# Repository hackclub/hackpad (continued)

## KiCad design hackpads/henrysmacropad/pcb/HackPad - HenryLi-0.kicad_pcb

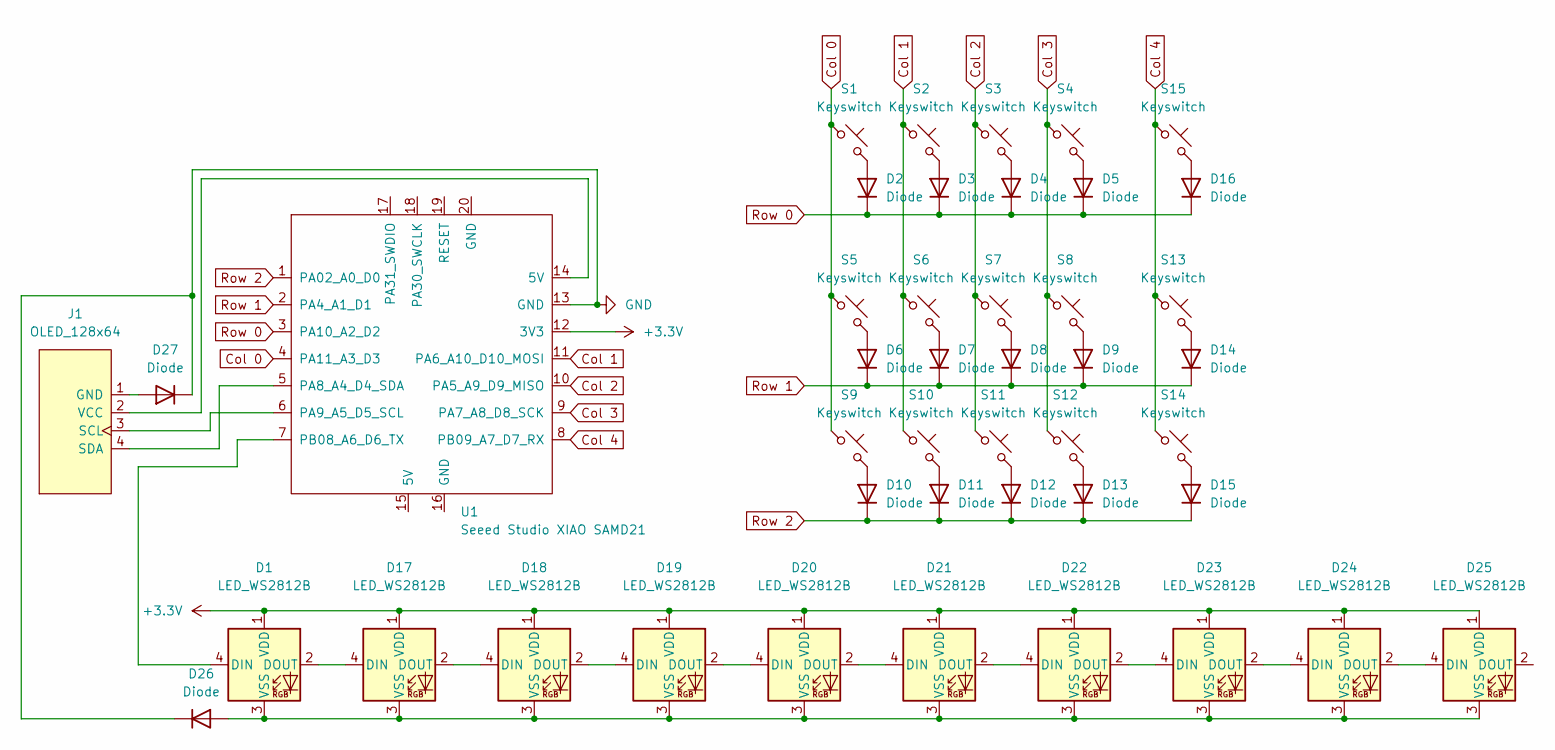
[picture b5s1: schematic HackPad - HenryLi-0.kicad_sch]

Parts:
D1, D17, D18, D19, D20, D21, D22, D23, D24, D25: LED_WS2812B
D2, D3, D4, D5, D6, D7, D8, D9, D10, D11, D12, D13, D14, D15, D16, D26, D27: Diode; Diode_DO-35
J1: OLED_128x64; SSD1306 128x64 OLED
S1, S2, S3, S4, S5, S6, S7, S8, S9, S10, S11, S12, S13, S14, S15: Keyswitch; SW_Cherry_MX_1.00u_PCB
U1: Seeed Studio XIAO SAMD21; XIAO-Generic-Thruhole-14P-2.54-21X17.8MM

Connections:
+3.3V: D1.1 (VDD), D17.1 (VDD), D18.1 (VDD), D19.1 (VDD), D20.1 (VDD), D21.1 (VDD), D22.1 (VDD), D23.1 (VDD), D24.1 (VDD), D25.1 (VDD), U1.12 (3V3)
Col 0: S1.1, S5.1, S9.1, U1.4 (PA11_A3_D3)
Col 1: S2.1, S6.1, S10.1, U1.11 (PA6_A10_D10_MOSI)
Col 2: S3.1, S7.1, S11.1, U1.10 (PA5_A9_D9_MISO)
Col 3: S4.1, S8.1, S12.1, U1.9 (PA7_A8_D8_SCK)
Col 4: S13.1, S14.1, S15.1, U1.8 (PB09_A7_D7_RX)
GND: D26.1 (K), D27.1 (K), U1.13 (GND)
unnamed: D1.4 (DIN), U1.7 (PB08_A6_D6_TX)
unnamed: D1.2 (DOUT), D17.4 (DIN)
unnamed: D1.3 (VSS), D17.3 (VSS), D18.3 (VSS), D19.3 (VSS), D20.3 (VSS), D21.3 (VSS), D22.3 (VSS), D23.3 (VSS), D24.3 (VSS), D25.3 (VSS), D26.2 (A)
unnamed: D2.2 (A), S1.2
unnamed: D3.2 (A), S2.2
unnamed: D4.2 (A), S3.2
unnamed: D5.2 (A), S4.2
unnamed: D6.2 (A), S5.2
unnamed: D7.2 (A), S6.2
unnamed: D8.2 (A), S7.2
unnamed: D9.2 (A), S8.2
unnamed: D10.2 (A), S9.2
unnamed: D11.2 (A), S10.2
unnamed: D12.2 (A), S11.2
unnamed: D13.2 (A), S12.2
unnamed: D14.2 (A), S13.2
unnamed: D15.2 (A), S14.2
unnamed: D16.2 (A), S15.2
unnamed: D17.2 (DOUT), D18.4 (DIN)
unnamed: D18.2 (DOUT), D19.4 (DIN)
unnamed: D19.2 (DOUT), D20.4 (DIN)
unnamed: D20.2 (DOUT), D21.4 (DIN)
unnamed: D21.2 (DOUT), D22.4 (DIN)
unnamed: D22.2 (DOUT), D23.4 (DIN)
unnamed: D23.2 (DOUT), D24.4 (DIN)
unnamed: D24.2 (DOUT), D25.4 (DIN)
unnamed: D27.2 (A), J1.1 (GND)
unnamed: J1.3 (SCL), U1.6 (PA9_A5_D5_SCL)
unnamed: J1.4 (SDA), U1.5 (PA8_A4_D4_SDA)
unnamed: J1.2 (VCC), U1.14 (5V)
Row 0: D2.1 (K), D3.1 (K), D4.1 (K), D5.1 (K), D16.1 (K), U1.3 (PA10_A2_D2)
Row 1: D6.1 (K), D7.1 (K), D8.1 (K), D9.1 (K), D14.1 (K), U1.2 (PA4_A1_D1)
Row 2: D10.1 (K), D11.1 (K), D12.1 (K), D13.1 (K), D15.1 (K), U1.1 (PA02_A0_D0)

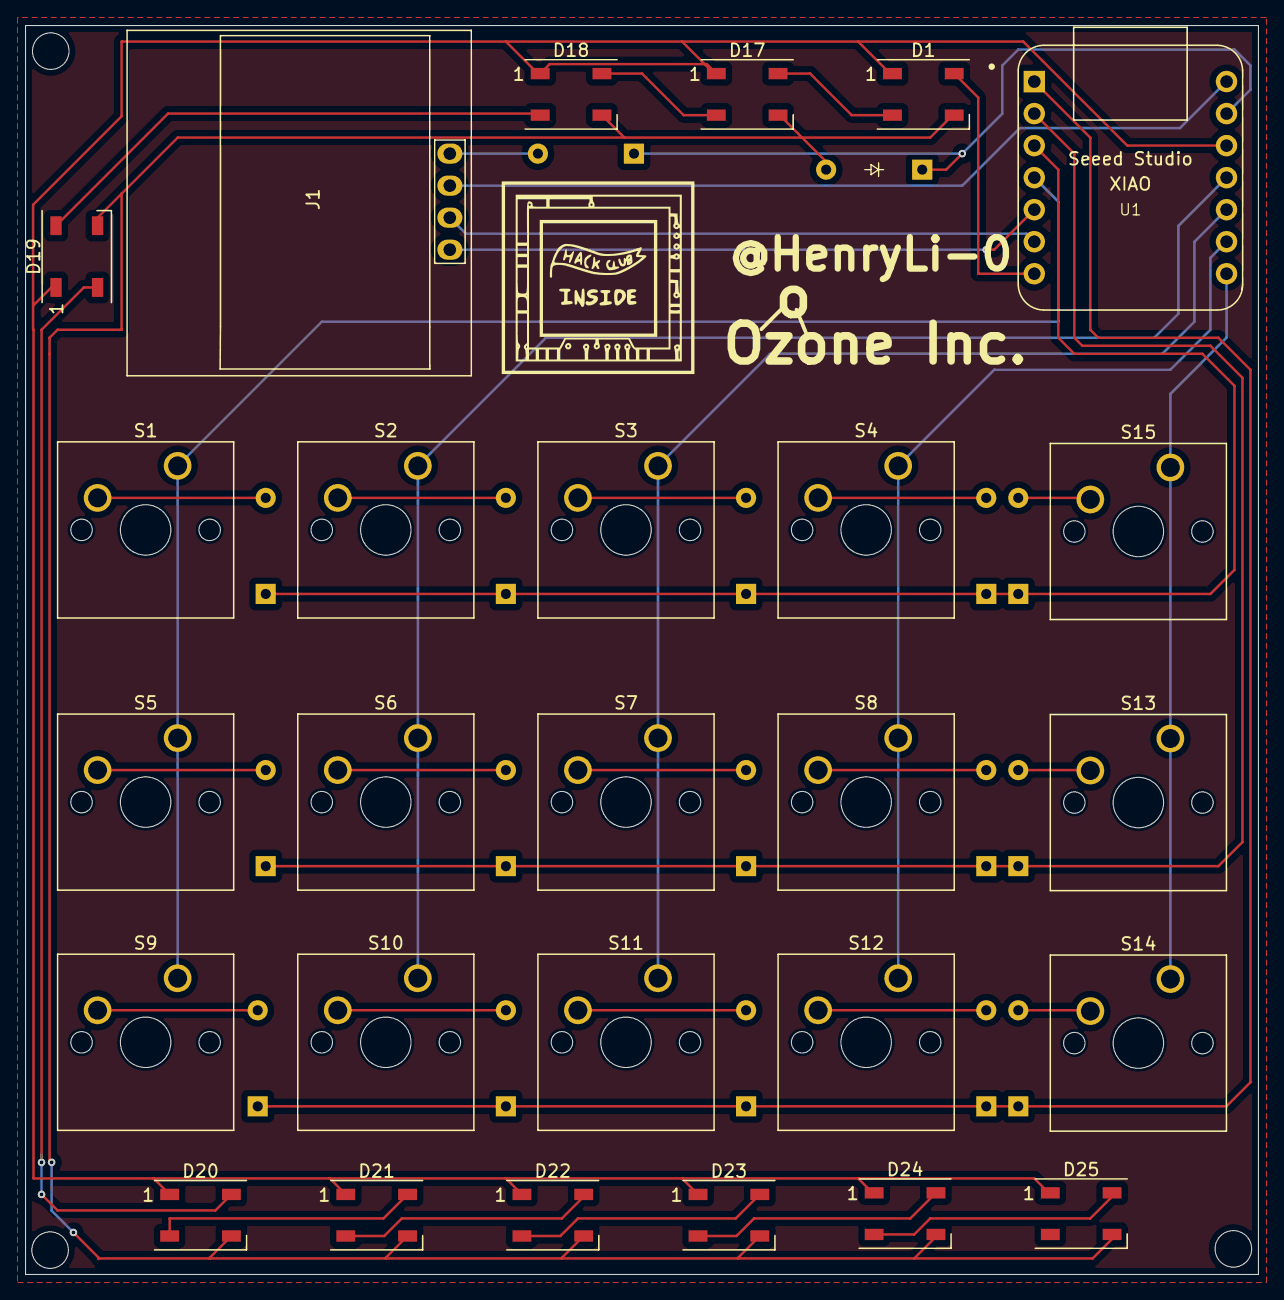
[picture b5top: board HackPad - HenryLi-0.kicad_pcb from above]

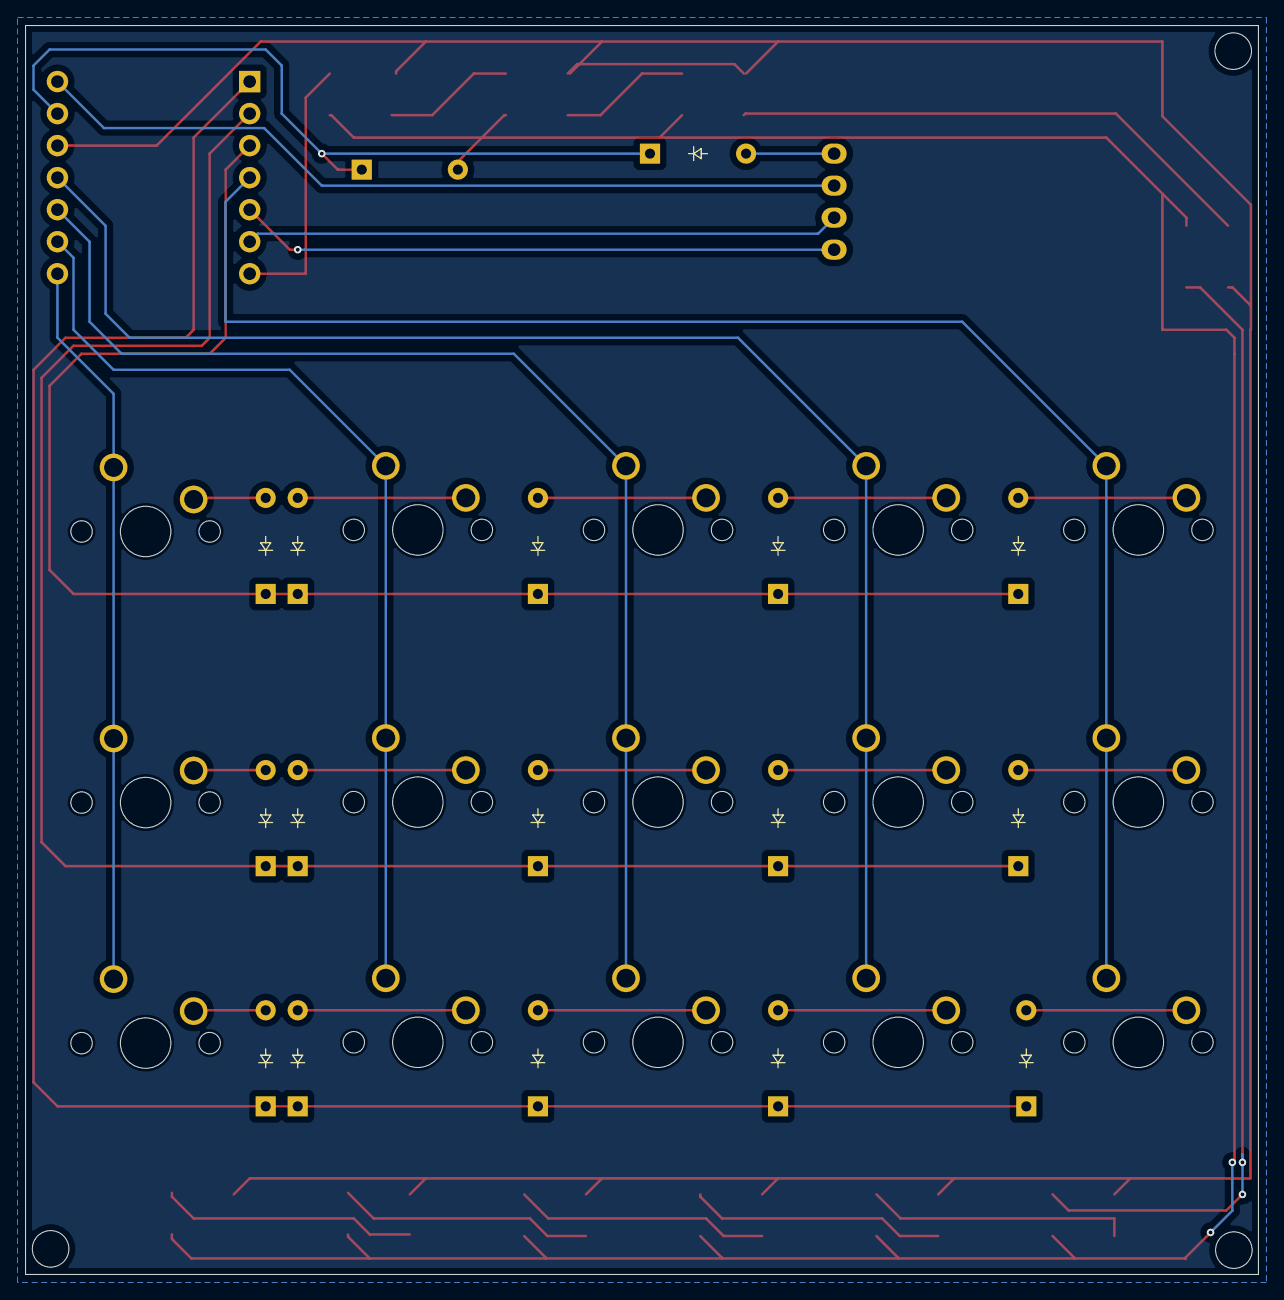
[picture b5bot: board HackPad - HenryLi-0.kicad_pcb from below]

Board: 2 copper layers, 97.8 x 99.1 mm, 44 parts (16 on the bottom side), 40 nets.

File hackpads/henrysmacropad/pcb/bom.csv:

Designator,Footprint,Quantity,Value,LCSC Part #
"D1, D17, D18, D19, D20, D21, D22, D23, D24, D25",LED_WS2812B,10,LED_WS2812B,
"D10, D11, D12, D13, D14, D15, D16, D2, D26, D27, D3, D4, D5, D6, D7, D8, D9",Diode_DO-35,17,Diode,
J1,SSD1306 128x64 OLED,1,OLED_128x64,
"S1, S10, S11, S12, S13, S14, S15, S2, S3, S4, S5, S6, S7, S8, S9",SW_Cherry_MX_1.00u_PCB,15,Keyswitch,
U1,XIAO-Generic-Thruhole-14P-2.54-21X17.8MM,1,Seeed Studio XIAO SAMD21,

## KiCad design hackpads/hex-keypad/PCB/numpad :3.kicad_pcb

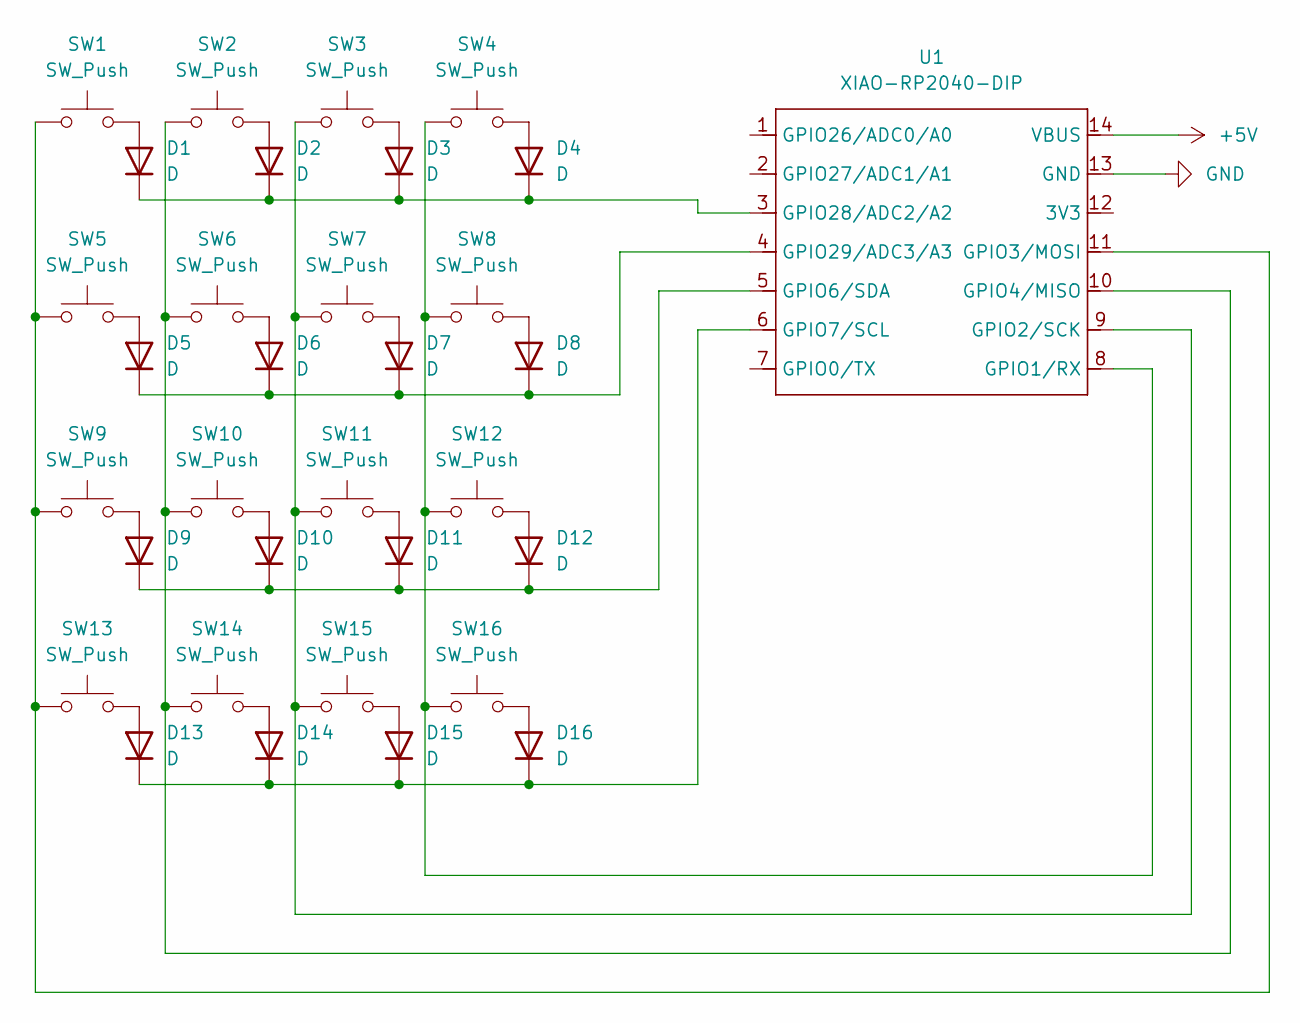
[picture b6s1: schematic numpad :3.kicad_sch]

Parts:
D1, D2, D3, D4, D5, D6, D7, D8, D9, D10, D11, D12, D13, D14, D15, D16: D; D_DO-35_SOD27_P7.62mm_Horizontal
SW1, SW2, SW3, SW4, SW5, SW6, SW7, SW8, SW9, SW10, SW11, SW12, SW13, SW14, SW15, SW16: SW_Push; MX-Solderable-1U
U1: XIAO-RP2040-DIP

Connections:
+5V: U1.14 (VBUS)
GND: U1.13 (GND)
unnamed: D1.2 (A), SW1.2
unnamed: D1.1 (K), D2.1 (K), D3.1 (K), D4.1 (K), U1.3 (GPIO28/ADC2/A2)
unnamed: D2.2 (A), SW2.2
unnamed: D3.2 (A), SW3.2
unnamed: D4.2 (A), SW4.2
unnamed: D5.2 (A), SW5.2
unnamed: D5.1 (K), D6.1 (K), D7.1 (K), D8.1 (K), U1.4 (GPIO29/ADC3/A3)
unnamed: D6.2 (A), SW6.2
unnamed: D7.2 (A), SW7.2
unnamed: D8.2 (A), SW8.2
unnamed: D9.2 (A), SW9.2
unnamed: D10.2 (A), SW10.2
unnamed: D9.1 (K), D10.1 (K), D11.1 (K), D12.1 (K), U1.5 (GPIO6/SDA)
unnamed: D11.2 (A), SW11.2
unnamed: D12.2 (A), SW12.2
unnamed: D13.2 (A), SW13.2
unnamed: D13.1 (K), D14.1 (K), D15.1 (K), D16.1 (K), U1.6 (GPIO7/SCL)
unnamed: D14.2 (A), SW14.2
unnamed: D15.2 (A), SW15.2
unnamed: D16.2 (A), SW16.2
unnamed: SW4.1, SW8.1, SW12.1, SW16.1, U1.8 (GPIO1/RX)
unnamed: SW3.1, SW7.1, SW11.1, SW15.1, U1.9 (GPIO2/SCK)
unnamed: SW1.1, SW5.1, SW9.1, SW13.1, U1.11 (GPIO3/MOSI)
unnamed: SW2.1, SW6.1, SW10.1, SW14.1, U1.10 (GPIO4/MISO)

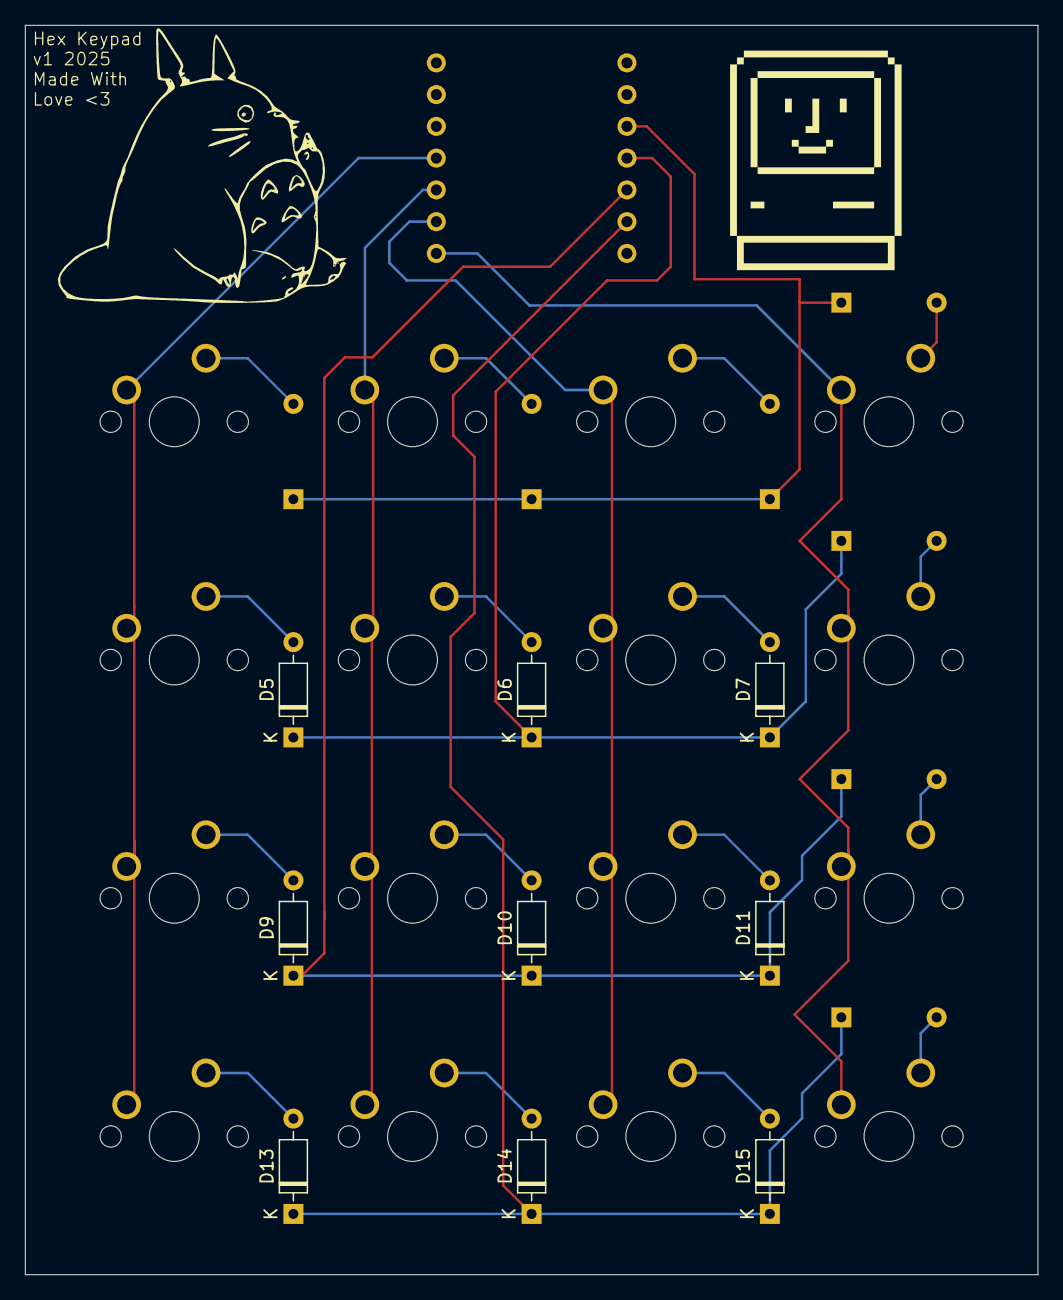
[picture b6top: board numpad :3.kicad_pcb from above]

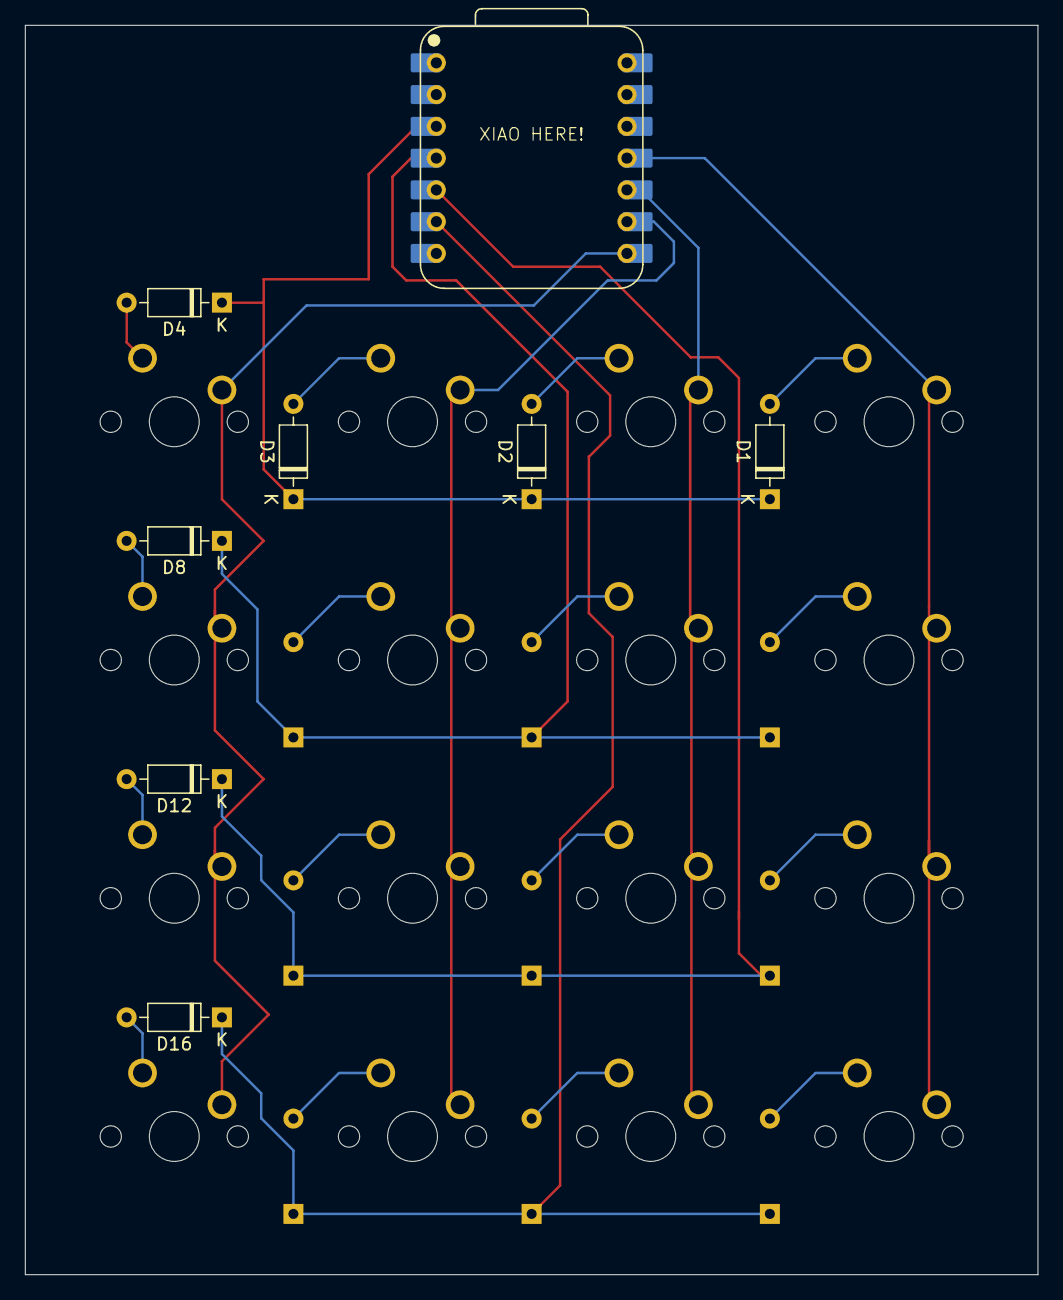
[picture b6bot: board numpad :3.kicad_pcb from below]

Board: 2 copper layers, 81.0 x 99.9 mm, 33 parts (8 on the bottom side), 24 nets.

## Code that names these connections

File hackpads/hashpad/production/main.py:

import board
import busio
import time
import board
from rainbowio import colorwheel

from kmk.kmk_keyboard import KMKKeyboard
from kmk.keys import KC
from kmk.scanners import DiodeOrientation
from kmk.modules.macros import Macros
from kmk.extensions.display import Display, TextEntry, ImageEntry
from kmk.extensions.display.ssd1306 import SSD1306
from kmk.extensions.RGB import RGB
from kmk.extensions.rgb import AnimationModes
from kmk.scanners.keypad import KeysScanner
from kmk.modules.macros import Press, Release, Tap, Macros
COL0 = board.D0;
COL1 = board.D1;
COL2 = board.D2; 
ROW0 = board.D0;
ROW1 = board.D6;
ROW2 = board.D7;
LED_PIN = board.D9;

bus = busio.I2C(board.SCL, board.SDA);

driver = SSD1306(i2c=bus, device_address=0x3C);

display = Display(
    display=driver,
    width=128,
    height=64,
    dim_time=10,
    dim_target=0.2,
    off_time=1200,
    brightness=0.7
);

keyboard = KMKKeyboard();

macros = Macros();
keyboard.modules.append(macros);
keyboard.extensions.append(display);

keyboard.col_pins = (COL0, COL1, COL2, COL3);
keyboard.row_pins = (ROW0, ROW1, ROW2, ROW3);
keyboard.diode_orientation = DiodeOrientation.COL2ROW;

rgb = RGB(pixel_pin=board.D10, num_pixels=9, animation_speed=1, animation_mode=AnimationModes.SWIRL)
keyboard.extensions.append(rgb)

keyboard.keymap = [
    [A, B, C,
     E, F, G,
     I, J, K],
];

if __name__ == '__main__':
    keyboard.go();
